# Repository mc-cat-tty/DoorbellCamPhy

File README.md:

# DoorbellCamPhy
## Notifier PCB
[Schematic](NotifierPcb/Exports/NotifierPcbSchematic.pdf)

[Board](NotifierPcb/Exports/NotifierPcbBoard.pdf)

<p>

 <br>

</p>

## Notifier PCB end result

## Camera holder
[3D Model](Holder/holderv24.stl)

<p>

 <br>
 
</p>

## Rasperry case base
[3D Model](Base/base.stl)

## Raspberry case columns
[3D Model](Columns/column.stl)

<p>

 <br>
 
</p>

## Raspberry case angle brackets
[3D Model](AngleBracket/angle_bracket.stl)

## Raspberry case rooftop support
[3D Model](RooftopSupport/rooftop_support.stl)

## Raspberry case IRL

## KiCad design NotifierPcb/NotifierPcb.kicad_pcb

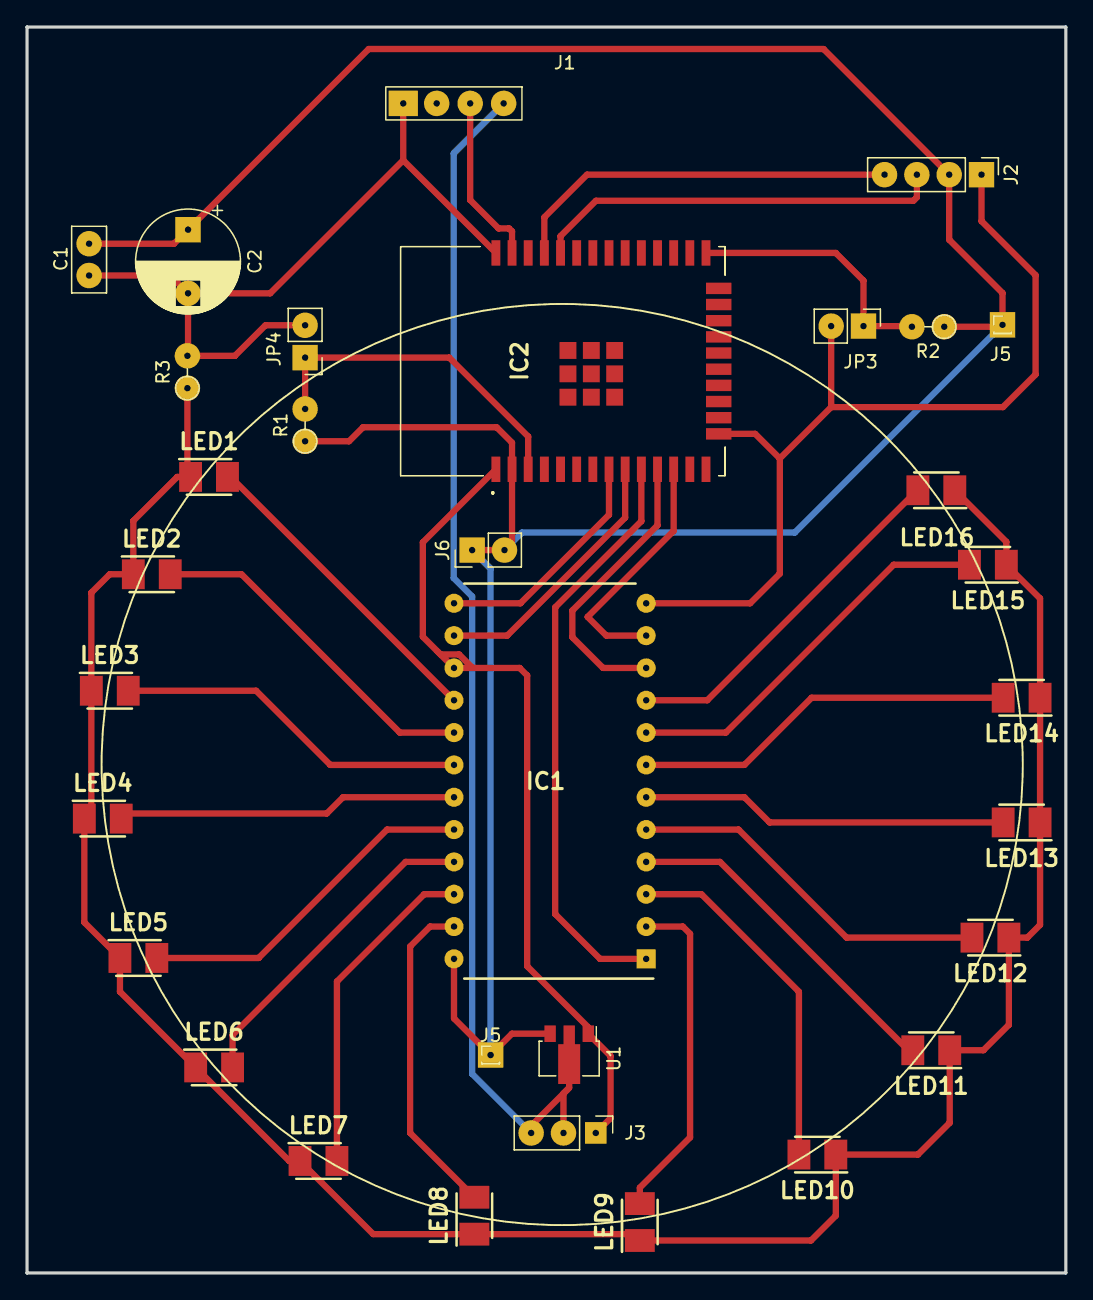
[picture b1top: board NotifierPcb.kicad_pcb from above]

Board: 2 copper layers, 81.6 x 97.9 mm, 32 parts (0 on the bottom side), 30 nets.

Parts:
C1: 0.1uF; C_Disc_D5.0mm_W2.5mm_P2.50mm
C2: 4.7uF; CP_Radial_D8.0mm_P5.00mm
IC1: CD4067BEE4; DIP1080W53P254L3104H508Q24N
IC2: ESP32-WROOM-32E__8MB_; ESP32WROOM32E8MB
J1: RC_433_MHZ_RF; RC_433_RX
J2: UART_Conn; PinHeader_1x04_P2.54mm_Vertical
J3: Power; PinHeader_1x03_P2.54mm_Vertical
J5, J5#2: Vcc; PinHeader_1x01_P1.00mm_Vertical
J6: Vcc; PinHeader_1x02_P2.54mm_Vertical
JP3: Boot_Jumper_Download; PinHeader_1x02_P2.54mm_Vertical
JP4: Enable_Jumper; PinHeader_1x02_P2.54mm_Vertical
LED1, LED2, LED3, LED4, LED5, LED6, LED7, LED8, LED9, LED10, LED11, LED12, LED13, LED14, LED15, LED16: PLCC2 3528; LEDM3528X210N
R1, R2: 10kΩ; R_Axial_DIN0204_L3.6mm_D1.6mm_P2.54mm_Vertical
R3: 100Ω; R_Axial_DIN0204_L3.6mm_D1.6mm_P2.54mm_Vertical
U1: HT75xx-1-SOT89; SOT-89-3

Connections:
+3.3V: C1.1, C2.1, IC1.24 (VDD), IC2.2 (3V3), J2.2, J5.1, J5#2.1, J6.1, J6.2, R1.1, U1.3 (VOUT)
+5V: J1.1 (VCC), J3.2, J3.3, U1.2 (VIN)
BIT0: IC1.10 (A), IC2.11 (IO26)
BIT1: IC1.11 (B), IC2.12 (IO27)
BIT2: IC1.14 (C), IC2.9 (IO33)
BIT3: IC1.13 (D), IC2.8 (IO32)
BOOT: IC2.25 (IO0), JP3.1 (A), R2.2
DEMUX_IN: IC1.1 (COMMON_OUT/IN), IC2.10 (IO25)
ESP32_EN: IC2.3 (EN), JP4.1 (A)
GND: C1.2, C2.2, IC1.12 (VSS), IC1.15 (INHIBIT), IC2.1 (GND_1), IC2.15 (GND_2), IC2.38 (GND_3), IC2.39 (GND_4), IC2.40 (GND_5), IC2.41 (GND_6), IC2.42 (GND_7), IC2.43 (GND_8), IC2.44 (GND_9), IC2.45 (GND_10), IC2.46 (GND_11), IC2.47 (GND_12), J1.4 (GND), J2.1, J3.1, JP3.2 (B), JP4.2 (B), R3.2, U1.1 (GND)
LED0: IC1.9 (CHANNEL_IN/OUT_0), LED16.2
LED1: IC1.8 (CHANNEL_IN/OUT_1), LED15.2
LED2: IC1.7 (CHANNEL_IN/OUT_2), LED14.2
LED3: IC1.6 (CHANNEL_IN/OUT_3), LED13.2
LED4: IC1.5 (CHANNEL_IN/OUT_4), LED12.2
LED5: IC1.4 (CHANNEL_IN/OUT_5), LED11.2
LED6: IC1.3 (CHANNEL_IN/OUT_6), LED10.2
LED7: IC1.2 (CHANNEL_IN/OUT_7), LED9.2
LED8: IC1.23 (CHANNEL_IN/OUT_8), LED8.2
LED9: IC1.22 (CHANNEL_IN/OUT_9), LED7.2
LED10: IC1.21 (CHANNEL_IN/OUT_10), LED6.2
LED11: IC1.20 (CHANNEL_IN/OUT_11), LED5.2
LED12: IC1.19 (CHANNEL_IN/OUT_12), LED4.2
LED13: IC1.18 (CHANNEL_IN/OUT_13), LED3.2
LED14: IC1.17 (CHANNEL_IN/OUT_14), LED2.2
LED15: IC1.16 (CHANNEL_IN/OUT_15), LED1.2
unnamed: LED1.1, LED2.1, LED3.1, LED4.1, LED5.1, LED6.1, LED7.1, LED8.1, LED9.1, LED10.1, LED11.1, LED12.1, LED13.1, LED14.1, LED15.1, LED16.1, R3.1
RX: IC2.37 (IO23), J1.2 (DATA)
UART_RX: IC2.34 (RXD0), J2.3
UART_TX: IC2.35 (TXD0), J2.4

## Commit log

2022-06-16 create column 3d model
2022-06-16 create base 3d model
2022-06-16 update readme file
2022-06-16 fix typo
2022-06-24 add rooftop support and angular brackets
2022-06-25 kickstart pcb design
2022-07-09 add case irl
2022-07-09 upload images
2022-07-09 fix file extension
2022-07-29 done schematic
2022-07-29 label table areas
2022-07-29 add annotations
2022-07-29 wokring on pcb
2022-07-29 plot pcb
2022-07-30 arrange leds in circle, add missing components
2022-07-30 done pcb beta version
2022-07-30 add keepout zone, ground plane£
2022-07-30 move external margin to Edge.Cuts
2022-07-30 exports pcb sheets
2022-07-30 replate embed with links
2022-07-30 add newline
2022-07-30 export new images
2022-07-30 plot production files
2022-07-30 edit readme
2022-08-07 make pads bigger
2022-08-07 add extrusions
2022-11-12 fixing strapping pins for download mode
2022-11-13 new configuratio for boot pins selection
2022-11-13 enlarge cd4067 pads
2022-11-13 add gnd for cd4067
2022-11-14 reroute GND for headers
2022-11-14 trying to fix
2022-11-15 enlarge pads
2022-11-24 remove unused flag selectors (default pin state)
2022-11-24 FIX: using only-input pin
2022-11-28 add pullup resistor for strapping pins
2022-11-29 control demux input
2023-01-19 power rf receiver with 5V
2023-01-29 add animation to readme
2023-01-29 upload animation
2023-01-29 embed gif with img tag
2023-01-29 make animation shorter
2023-02-15 Add PcbEnclosure via upload
